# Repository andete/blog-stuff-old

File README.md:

blog-stuff
==========

Miscelaneous code, schematics, ... from blog posts.

Unless otherwise stated in the file, all code is GPLv3+ licensed
and all schematic and board files are CC0 licensed.

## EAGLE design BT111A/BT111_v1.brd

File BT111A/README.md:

BT111-A Bluetooth Smart Ready (BT+Low Energy) USB dongle
========================================================

* eagle schematic and board

related blog posts:

* http://joost.damad.be/

related tindie product:

* https://www.tindie.com/products/andete/bluetooth-smart-ready-btbtle-bluegiga-bt111-a-usb-dongle/

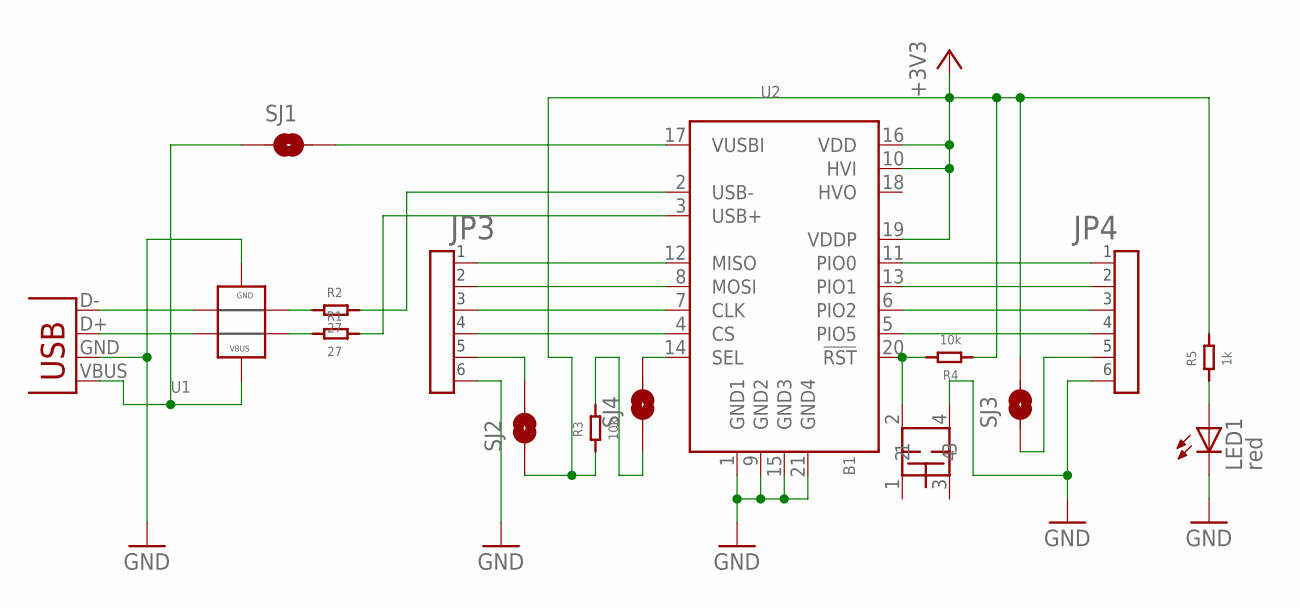
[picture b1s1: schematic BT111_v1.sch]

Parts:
B1: BUTTON_ALPS_5.2MM_SMD; BUTTON_ALPS_SMD_5.2MM_SKQG
JP1: USB-A-H
JP3, JP4: PIN1X6PTH_SMALL; PIN_1X6_S
LED1: red; CHIP-LED0805
R1, R2: 27; 0603
R3, R4: 10k; 0603
R5: 1k; 0603
SJ1: USBPOW; SJ_2S
SJ2: SPIPOW; SJ_2S-NO
SJ3: PIOPOW; SJ_2S-NO
SJ4: PCMSEL; SJ_2S-NO
U1: ST_USBLC6-2; SOT-23-6L
U2: BT111

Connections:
+3V3: R3.1, R4.1, R5.2, SJ2.1, SJ3.2, U2.10 (HVI), U2.16 (VDD), U2.19 (VDDP)
CLK: JP3.3, U2.7 (CLK)
CS: JP3.4, U2.4 (CS)
GND: B1.4, JP1.GND (VBUS), JP3.6, JP4.6, LED1.C, U1.2 (GND), U2.1 (GND1), U2.9 (GND2), U2.15 (GND3), U2.21 (GND4)
MISO: JP3.1, U2.12 (MISO)
MOSI: JP3.2, U2.8 (MOSI)
unnamed: LED1.A, R5.1
unnamed: JP3.5, SJ2.2
unnamed: JP4.5, SJ3.1
unnamed: JP1.D- (D+), U1.3 (IO2A)
unnamed: JP1.D+ (D-), U1.1 (IO1A)
unnamed: R2.1, U1.4 (IO2B)
unnamed: R1.1, U1.6 (IO1B)
PIO0: JP4.1, U2.11 (PIO0)
PIO1: JP4.2, U2.13 (PIO1)
PIO2: JP4.3, U2.6 (PIO2)
PIO5: JP4.4, U2.5 (PIO5)
RST: B1.2, R4.2, U2.20 (!RST)
SEL: SJ4.2, U2.14 (SEL)
SEL2: R3.2, SJ4.1
USB+: R1.2, U2.3 (USB+)
USB-: R2.2, U2.2 (USB-)
VBUS1: JP1.VBUS (GND), SJ1.1, U1.5 (VBUS)
VUSBINT: SJ1.2, U2.17 (VUSBI)

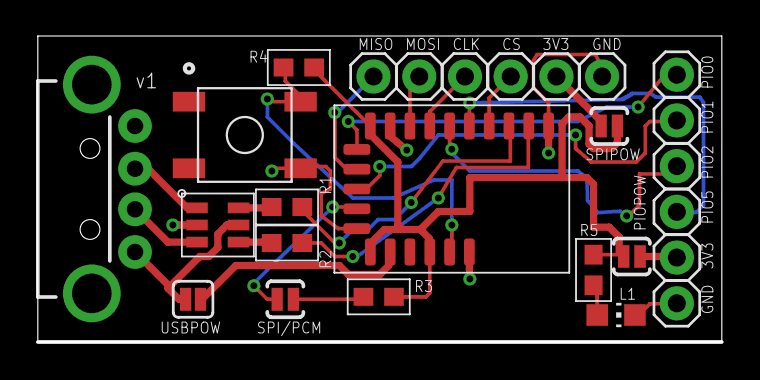
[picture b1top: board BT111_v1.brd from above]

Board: 2 copper layers, 38.0 x 16.9 mm, 16 parts (0 on the bottom side), 24 nets.

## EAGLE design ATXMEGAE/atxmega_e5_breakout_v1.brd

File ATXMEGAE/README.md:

Atxmega32E5 stuff
=================

* example code
* breakout eagle schematic and board
* avr related files to get it compilable in linux

related blog posts:

* http://joost.damad.be/2013/08/using-atxmega32e5-under-linux.html

related tindie product:

* https://www.tindie.com/products/andete/atxmega32e5-breakout-board/

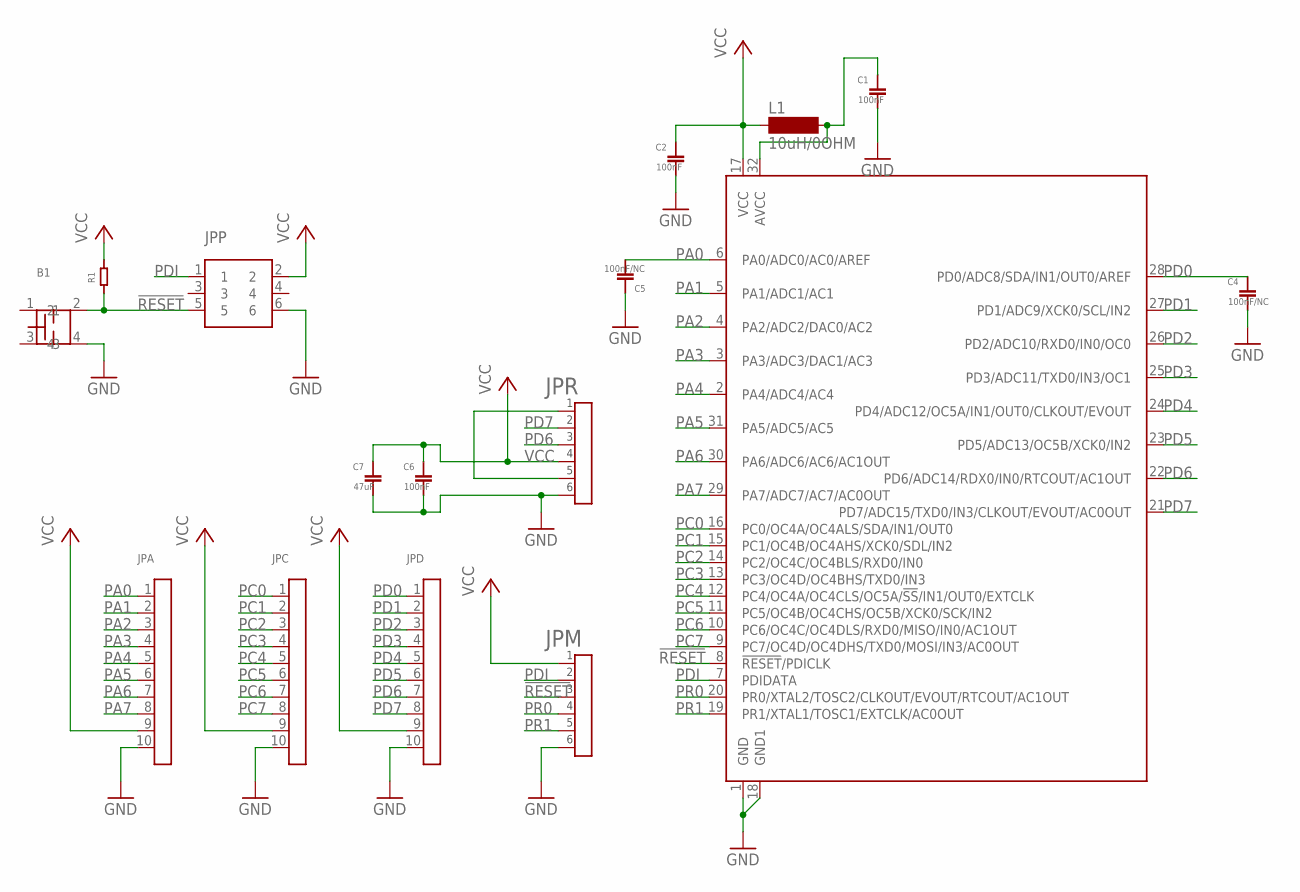
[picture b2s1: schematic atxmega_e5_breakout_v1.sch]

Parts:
B1: BUTTON_ALPS_5.2MM_SMD; BUTTON_ALPS_SMD_5.2MM_SKQG
C1, C2, C6: 100nF; 0603
C4, C5: 100nF/NC; 0603
C7: 47uF; 1206
JPA: PIN1X10PTH_S; PIN_1X10_S
JPC: PIN1X10PTH_S; PIN_1X10_S
JPD: PIN1X10PTH_S; PIN_1X10_S
JPM: PIN1X6PTH_SMALL; PIN_1X6_S
JPP: PIN2X3ALT_S; PIN_2X3_ALT_S
JPR: PIN1X6PTH_SMALL; PIN_1X6_S
L1: 10uH/0OHM; SM-1206
R1: RESISTOR0603; 0603
U1: ATXMEGAE5AU; TQFP32

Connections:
!RESET: B1.2, JPM.3, JPP.5, R1.1, U1.8 (!RESET!/PDICLK)
AVCC: C1.2 (1), L1.2, U1.32 (AVCC)
GND: B1.4, C1.1 (2), C2.1 (2), C4.1 (2), C5.2 (1), C6.1 (2), C7.2, JPA.10, JPC.10, JPD.10, JPM.6, JPP.6, JPR.6, U1.1 (GND), U1.18 (GND1)
unnamed: JPR.1, JPR.5
PA0: C5.1 (2), JPA.1, U1.6 (PA0/ADC0/AC0/AREF)
PA1: JPA.2, U1.5 (PA1/ADC1/AC1)
PA2: JPA.3, U1.4 (PA2/ADC2/DAC0/AC2)
PA3: JPA.4, U1.3 (PA3/ADC3/DAC1/AC3)
PA4: JPA.5, U1.2 (PA4/ADC4/AC4)
PA5: JPA.6, U1.31 (PA5/ADC5/AC5)
PA6: JPA.7, U1.30 (PA6/ADC6/AC6/AC1OUT)
PA7: JPA.8, U1.29 (PA7/ADC7/AC7/AC0OUT)
PC0: JPC.1, U1.16 (PC0/OC4A/OC4ALS/SDA/IN1/OUT0)
PC1: JPC.2, U1.15 (PC1/OC4B/OC4AHS/XCK0/SDL/IN2)
PC2: JPC.3, U1.14 (PC2/OC4C/OC4BLS/RXD0/IN0)
PC3: JPC.4, U1.13 (PC3/OC4D/OC4BHS/TXD0/IN3)
PC4: JPC.5, U1.12 (PC4/OC4A/OC4CLS/OC5A/!SS!/IN1/OUT0/EXTC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)
PC5: JPC.6, U1.11 (PC5/OC4B/OC4CHS/OC5B/XCK0/SCK/IN2)
PC6: JPC.7, U1.10 (PC6/OC4C/OC4DLS/RXD0/MISO/IN0/AC1OUT)
PC7: JPC.8, U1.9 (PC7/OC4D/OC4DHS/TXD0/MOSI/IN3/AC0OUT)
PD0: C4.2 (1), JPD.1, U1.28 (PD0/ADC8/SDA/IN1/OUT0/AREF)
PD1: JPD.2, U1.27 (PD1/ADC9/XCK0/SCL/IN2)
PD2: JPD.3, U1.26 (PD2/ADC10/RXD0/IN0/OC0)
PD3: JPD.4, U1.25 (PD3/ADC11/TXD0/IN3/OC1)
PD4: JPD.5, U1.24 (PD4/ADC12/OC5A/IN1/OUT0/CLKOUT/EVOUT)
PD5: JPD.6, U1.23 (PD5/ADC13/OC5B/XCK0/IN2)
PD6: JPD.7, JPR.3, U1.22 (PD6/ADC14/RDX0/IN0/RTCOUT/AC1OUT)
PD7: JPD.8, JPR.2, U1.21 (PD7/ADC15/TXD0/IN3/CLKOUT/EVOUT/AC0OUT)
PDI: JPM.2, JPP.1, U1.7 (PDIDATA)
PR0: JPM.4, U1.20 (PR0/XTAL2/TOSC2/CLKOUT/EVOUT/RTCOUT/AC1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)
PR1: JPM.5, U1.19 (PR1/XTAL1/TOSC1/EXTCLK/AC0OUT)
VCC: C2.2 (1), C6.2 (1), C7.1, JPA.9, JPC.9, JPD.9, JPM.1, JPP.2, JPR.4, L1.1, R1.2, U1.17 (VCC)

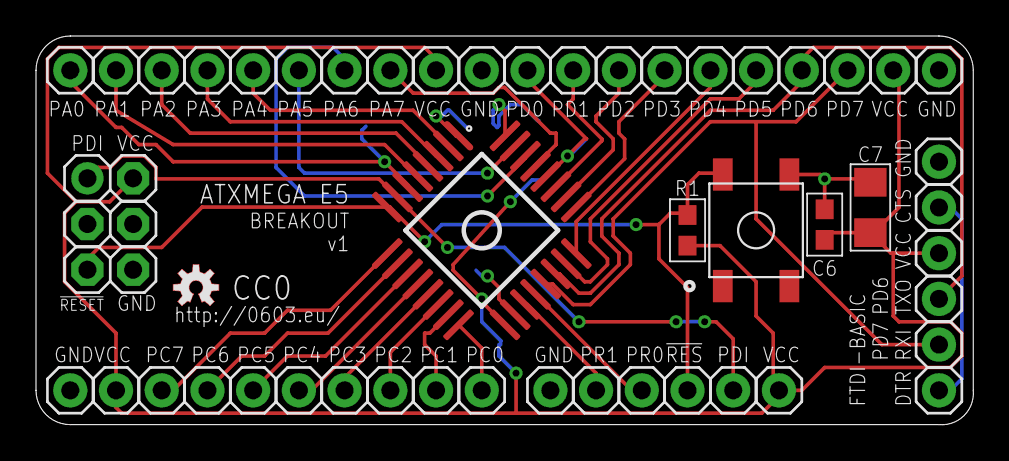
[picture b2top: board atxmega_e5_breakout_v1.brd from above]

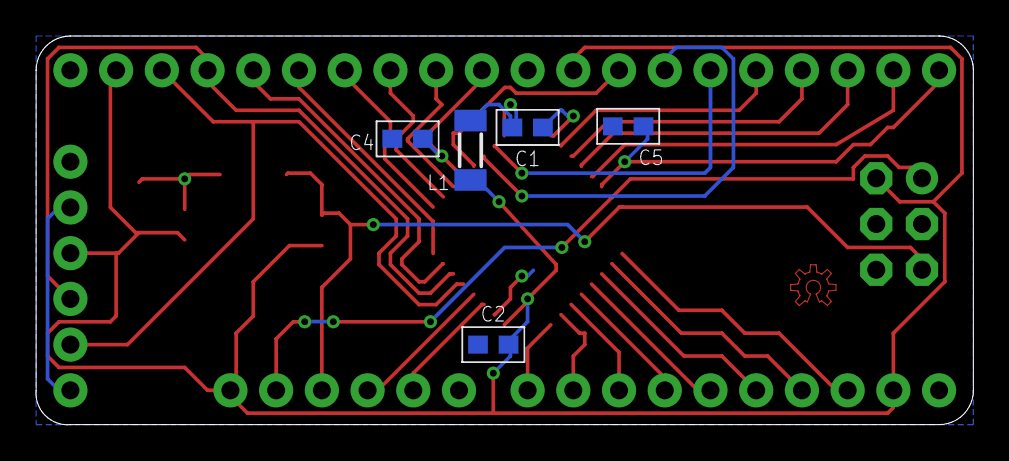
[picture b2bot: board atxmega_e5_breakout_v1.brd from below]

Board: 2 copper layers, 52.1 x 21.6 mm, 16 parts (5 on the bottom side), 32 nets.

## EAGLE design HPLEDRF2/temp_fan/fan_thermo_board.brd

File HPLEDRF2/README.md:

high power LED retrofit
=======================

related blog posts:

* http://joost.damad.be/2013/05/high-power-led-retrofit-part1.html
* http://joost.damad.be/2013/05/high-power-led-retrofit-part2.html
* http://joost.damad.be/2013/05/high-power-led-retrofit-part-3.html
* http://joost.damad.be/2013/05/high-power-led-retrofit-part-4.html

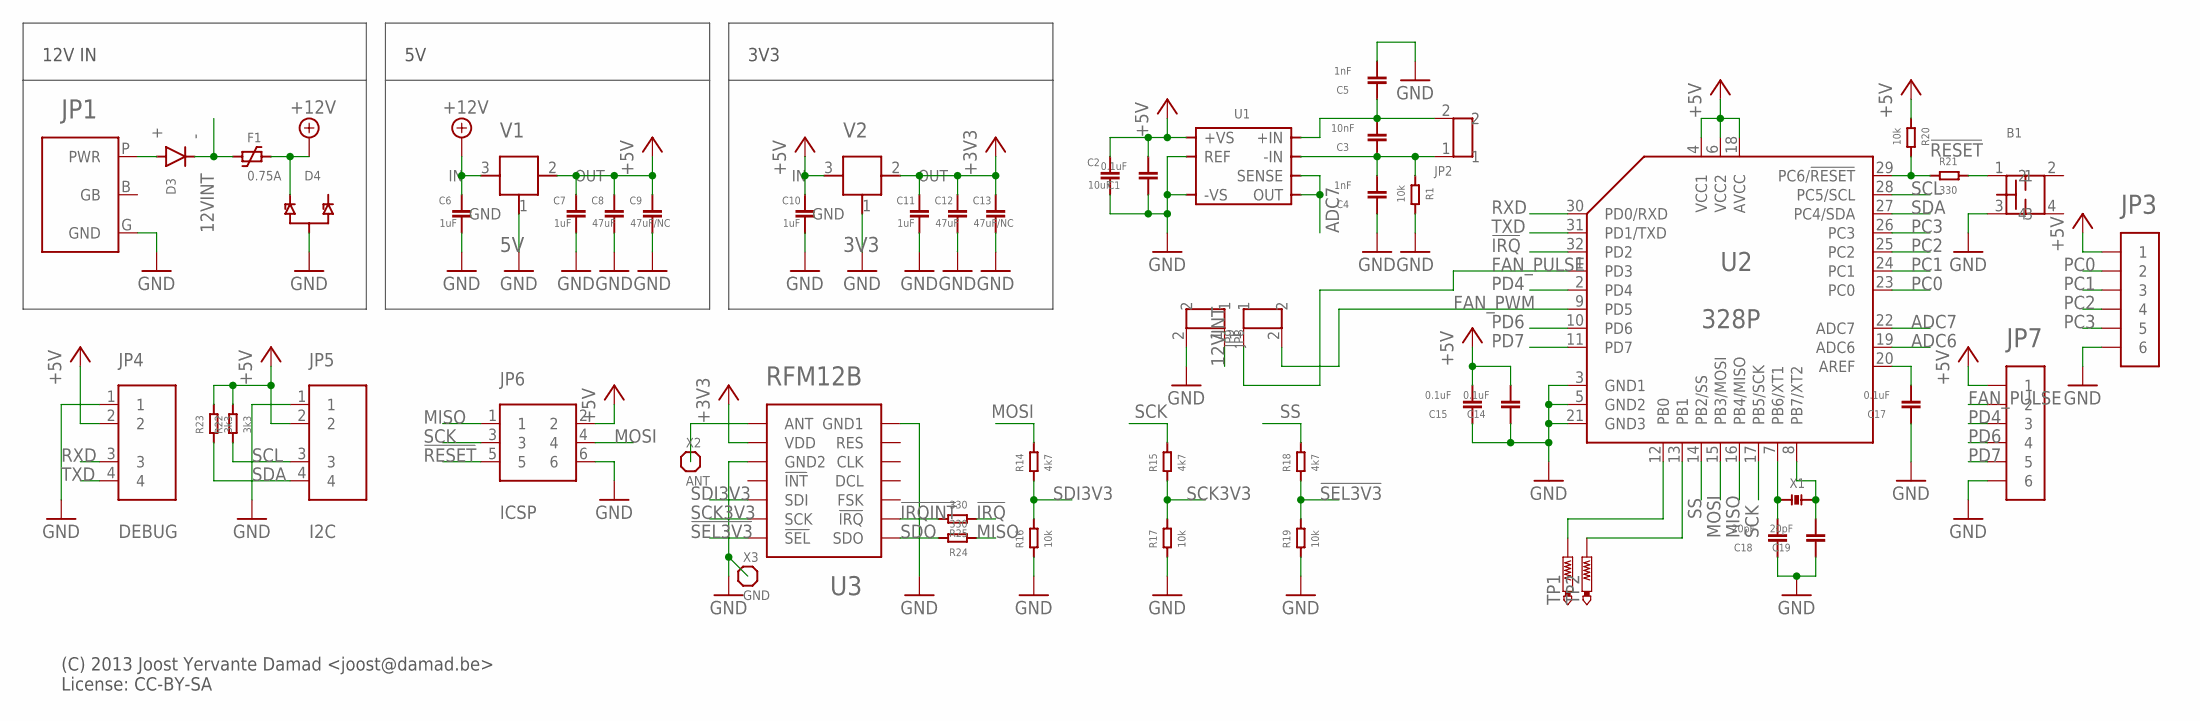
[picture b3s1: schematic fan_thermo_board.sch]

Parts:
B1: BUTTON_ALPS_5.2MM_SMD; BUTTON_ALPS_SMD_5.2MM_SKQG
C1, C14, C15, C17: 0.1uF; 0603@1
C2: 10uF; 1206
C3: 10nF; 0603@1
C4, C5: 1nF; 0603@1
C6, C7, C10, C11: 1uF; 0603
C8, C12: 47uF; 1206
C9, C13: 47uF/NC; 1206
C18, C19: 20pF; 0603@1
D3: DIODE; TAIW_SEM_DIODE
D4: DUAL_TVSSOT-23; SOT-23
F1: 0.75A; TE_POLYFUSE_1812
JP1: POWER_PLUG_2.1MM
JP2, JP8, JP9: WAGO500-2PIN; WAGO_500_SCREW_TERMINAL_2_PIN
JP3, JP7: PIN1X6; PIN_1X6
JP4: DEBUG; PIN_1X4
JP5: I2C; JST-S-4B-XH-A
JP6: ICSP; PIN_2X3_ALT
R1, R16, R17, R19, R20: 10k; 0603
R14, R15, R18: 4k7; 0603
R21, R24, R25: 330; 0603
R22, R23: 3k3; 0603
TP1, TP2: PTR1B1,27; B1,27
U1: AD8495; JEDEC_MO-187-AA
U2: 328P; TQFP32
U3: RFM12B
V1: 5V; SOT-23A
V2: 3V3; SOT-23A
X1: CRYSTAL; CRYSTAL_2-PAD_5X3.2MM
X2: ANT; PIN_1X1
X3: GND; PIN_1X1

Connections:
12VINT: D3.-, F1.1, JP8.1
!IRQ: R25.1, U2.32 (PD2)
!IRQINT: R25.2, U3.NIRQ (!IRQ)
!RESET: JP6.5, R20.2, R21.1, U2.29 (PC6/!RESET)
!SEL3V3: R18.1, R19.2, U3.NSEL (!SEL)
+3V3: C11.2 (1), C12.1, C13.1, U3.VDD, V2.2 (OUT)
+5V: C1.1 (2), C2.1, C7.2 (1), C8.1, C9.1, C10.2 (1), C14.1 (2), C15.1 (2), JP3.1, JP4.2, JP5.2, JP6.2, JP7.1, R20.1, R22.2, R23.2, U1.7 (+VS), U2.4 (VCC1), U2.6 (VCC2), U2.18 (AVCC), V1.2 (OUT), V2.3 (IN)
+12V: C6.2 (1), D4.1, F1.2, V1.3 (IN)
ADC6: U2.19 (ADC6)
ADC7: U1.5 (SENSE), U1.6 (OUT), U2.22 (ADC7)
FAN_PULSE: JP7.2, JP9.1, U2.1 (PD3)
FAN_PWM: JP9.2, U2.9 (PD5)
GND: B1.3, C1.2 (1), C2.2, C4.2 (1), C5.1 (2), C6.1 (2), C7.1 (2), C8.2, C9.2, C10.1 (2), C11.1 (2), C12.2, C13.2, C14.2 (1), C15.2 (1), C17.2 (1), C18.2 (1), C19.2 (1), D4.3 (G1), JP1.G (GND), JP3.6, JP4.1, JP5.1, JP6.6, JP7.6, JP8.2, R1.2, R16.1, R17.1, R19.1, U1.2 (REF), U1.3 (-VS), U2.3 (GND1), U2.5 (GND2), U2.21 (GND3), U3.GND@1 (GND1), U3.GND@2 (GND2), V1.1 (GND), V2.1 (GND), X3.1
IN+: C3.1 (2), C5.2 (1), JP2.2, U1.8 (+IN)
IN-: C3.2 (1), C4.1 (2), JP2.1, R1.1, U1.1 (-IN)
MISO: JP6.1, R24.1, U2.16 (PB4/MISO)
MOSI: JP6.4, R14.2, U2.15 (PB3/MOSI)
unnamed: TP2.TP, U2.13 (PB1)
unnamed: TP1.TP, U2.12 (PB0)
unnamed: D3.+, JP1.P (PWR)
unnamed: U3.ANT, X2.1
unnamed: C17.1 (2), U2.20 (AREF)
unnamed: B1.1, R21.2
unnamed: C18.1 (2), U2.7 (PB6/XT1), X1.1
unnamed: C19.1 (2), U2.8 (PB7/XT2), X1.2
PC0: JP3.2, U2.23 (PC0)
PC1: JP3.3, U2.24 (PC1)
PC2: JP3.4, U2.25 (PC2)
PC3: JP3.5, U2.26 (PC3)
PD4: JP7.3, U2.2 (PD4)
PD6: JP7.4, U2.10 (PD6)
PD7: JP7.5, U2.11 (PD7)
RXD: JP4.3, U2.30 (PD0/RXD)
SCK: JP6.3, R15.2, U2.17 (PB5/SCK)
SCK3V3: R15.1, R17.2, U3.SCK
SCL: JP5.3, R22.1, U2.28 (PC5/SCL)
SDA: JP5.4, R23.1, U2.27 (PC4/SDA)
SDI3V3: R14.1, R16.2, U3.SDI
SDO: R24.2, U3.SDO
SS: R18.2, U2.14 (PB2/SS)
TXD: JP4.4, U2.31 (PD1/TXD)

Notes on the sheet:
(C) 2013 Joost Yervante Damad <joost@damad.be> License: CC-BY-SA
3V3
12V IN

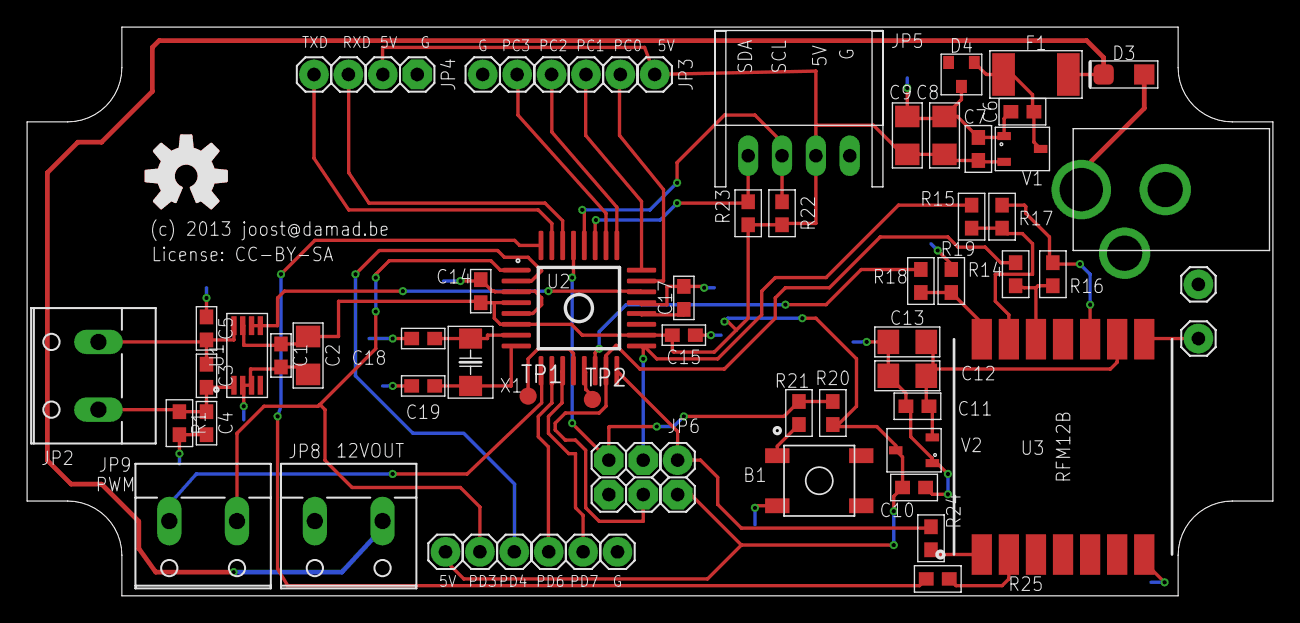
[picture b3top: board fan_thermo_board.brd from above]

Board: 4 copper layers, 92.0 x 42.0 mm, 54 parts (0 on the bottom side), 40 nets.

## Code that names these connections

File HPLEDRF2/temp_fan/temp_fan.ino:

/* -*- Mode: C; tab-width: 2; indent-tabs-mode: nil -*- */
// (c) 2013 Joost Yervante Damad <joost@damad.be>
// License: GPL

#include <JeeLib.h>
#include <Wire.h>

#include "../relay_pwm/settings.h"

// #define SECOND

#ifndef SECOND
#define RF_ID TEMP_FAN_RF_ID
#define MY_R_ID LED_PWM_RF_ID
#else
#define RF_ID TEMP_FAN_RF_ID2
#define MY_R_ID LED_PWM_RF_ID2
#endif

// PD3
#define FAN_PULSE 3
// PD5
#define FAN_PWM 5

// ADC7
#define TEMP_PIN A7

// ADC is 5.0/1024 volt per adc step
// ad8495 is 5mV/C
static const float reference_voltage = 5.0;
static const float adc_factor = (reference_voltage/1024)/(5E-3);

static inline bool rf_available() {
  return (rf12_recvDone() && rf12_crc == 0 && rf12_len >= 1);
}

static inline void rf_ack(const uint8_t cmd, const uint8_t reply_address) {
  static uint8_t data[3];
  data[0] = RF_ID;
  data[1] = reply_address;
  data[2] = cmd;
  rf12_sendStart(RF12_ACK_REPLY, data, sizeof data);
  rf12_sendWait(1);
}

volatile uint16_t pulse_count = 0;
static void pulse_interrupt() {
    ++pulse_count;
  }

static int8_t temperature = 0;
static uint8_t pwm_setting = 64;


static inline void send_data(const uint8_t reply_address) {
  static uint8_t data[7];
  data[0] = RF_ID;
  data[1] = reply_address;
  data[2] = CMD_TEMP_FAN_Q;
  data[3] = temperature;
  data[4] = pulse_count / 256;
  data[5] = pulse_count % 256;
  data[6] = pwm_setting;
  rf12_sendStart(0, data, sizeof data);
  rf12_sendWait(1);
  Serial.println("[send_data]");
}

static inline void set_pwm(const uint8_t reply_address, const uint8_t val) {
  pwm_setting = val;
  analogWrite(FAN_PWM, pwm_setting);
  rf_ack(CMD_SET_FAN_PWM, reply_address);
  Serial.println("[set_pwm]");
}

void setup() {
  // Serial
  Serial.begin(9600);
  Serial.print("Hello I am temp fan v"); Serial.println(VERSION);

  // RF
  rf12_initialize(RF_ID, RF12_868MHZ, RF_GROUP);
  Serial.print("RF ready at "); Serial.println(RF_ID);

  // PWM
  pinMode(FAN_PWM, OUTPUT);
  analogWrite(FAN_PWM, pwm_setting);

  // fan pulse
  attachInterrupt(1, pulse_interrupt, FALLING);

  // set ADC reference to internal 1.1V reference
  // internal ref is +- 0.1V
  // 5V Vreg is +-0.025V, so using the internal reference is far worse
  // analogReference(INTERNAL);
}


void loop() {
  static uint8_t lc = 0;
  if (rf_available()) {
    const uint8_t source = rf12_data[0];
    const uint8_t target = rf12_data[1];
    if (target == RF_ID || target == 0) {
      const uint8_t cmd = rf12_data[2];
      switch (cmd) {
        case CMD_TEMP_FAN_Q: send_data(source); break;
        case CMD_SET_FAN_PWM: set_pwm(source, rf12_data[3]); break;
      }
    } 
  }
  delay(100);
  ++lc;
  if (lc % (12 + 2*RF_ID) == 0) {
     // take temperature, check fan pulse
     const float raw_temp = analogRead(TEMP_PIN); // steps
     temperature = raw_temp * adc_factor;
     Serial.print(temperature); Serial.print(" "); Serial.println(pulse_count);
     send_data(MY_R_ID);
  }
}

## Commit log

2013-05-02 initial import HPLEDRF
2013-05-02 add readme
2013-05-02 cleanup (part1)
2013-05-02 cleanup (part2)
2013-05-02 cleanup (part3)
2013-05-02 cleanup (part4)
2013-05-02 cleanup (part5)
2013-05-02 cleanup (part6)
2013-05-02 swap on/off relay; send ack after using msg data or data is gone
2013-05-02 testing code; cleanup
2013-05-04 lower LED pwm frequency; add fan on/off pin; disable fan code; add NO_BEEP setting
2013-05-05 more fan control steps; more temperature measurement steps
2013-05-05 fan speed interpolated on temperature
2013-05-09 fan on/off handling code (done with high-side P-channel mosfet switching)
2013-05-09 log pulse fail counting
2013-05-21 add code for http://joost.damad.be/2012/10/software-serial-possible-alternative.html
2013-05-28 add NullSerial.h
2013-05-31 add BufferSerial
2013-05-31 update URL
2013-07-04 add initial relay_pwm sketch
2013-07-04 temp_fan sketch; initial layout
2013-07-04 basic functionality for temp_fan sketch
2013-07-05 cleanup temp_fan sketch
2013-07-05 externalize settings
2013-07-05 relay_pwm sketch mostly works
2013-07-05 log enable/disable of relay/LED
2013-07-05 tune defaults: fan_pwm:64; idle:30lc
2013-07-22 wrap up HPLEDRF2
2013-07-23 add schematic and board
2013-08-09 add avrdude.conf with atxmega16e5 definition
2013-08-09 add atxmega32e5 device signature
2013-08-10 make clear that this is avrdude 6 config file
2013-08-10 fix atxmega16e5 and atxmega32e5 memory layout info
2013-08-10 add avrdude5.conf (not working!)
2013-08-10 use C++ isof C; use atxmega32e5; remove avrdude5.conf; full working example :)
2013-08-10 add README.md; add for_avr-libc stuff; cosmetic fixes
2013-08-11 add links to README.md
2013-08-13 add BT111 stuff
2013-09-13 add images of bt111 breakout schematic
2013-09-13 explain licensing
2013-09-13 add CC0 license
2013-09-13 add pictures
2013-09-13 add kicad schematic and board
2013-09-13 add pdf of schematic
2013-12-14 add stm32f105 sample blink code

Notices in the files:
BT111A/BT111_v1.brd:
(C)2013 joost@damad.be
License: CC0
parts and their libraries:
SparkFun-Connectors: Licensing: CC v3.0 Share-Alike You are welcome to use this library for commercial purposes.
